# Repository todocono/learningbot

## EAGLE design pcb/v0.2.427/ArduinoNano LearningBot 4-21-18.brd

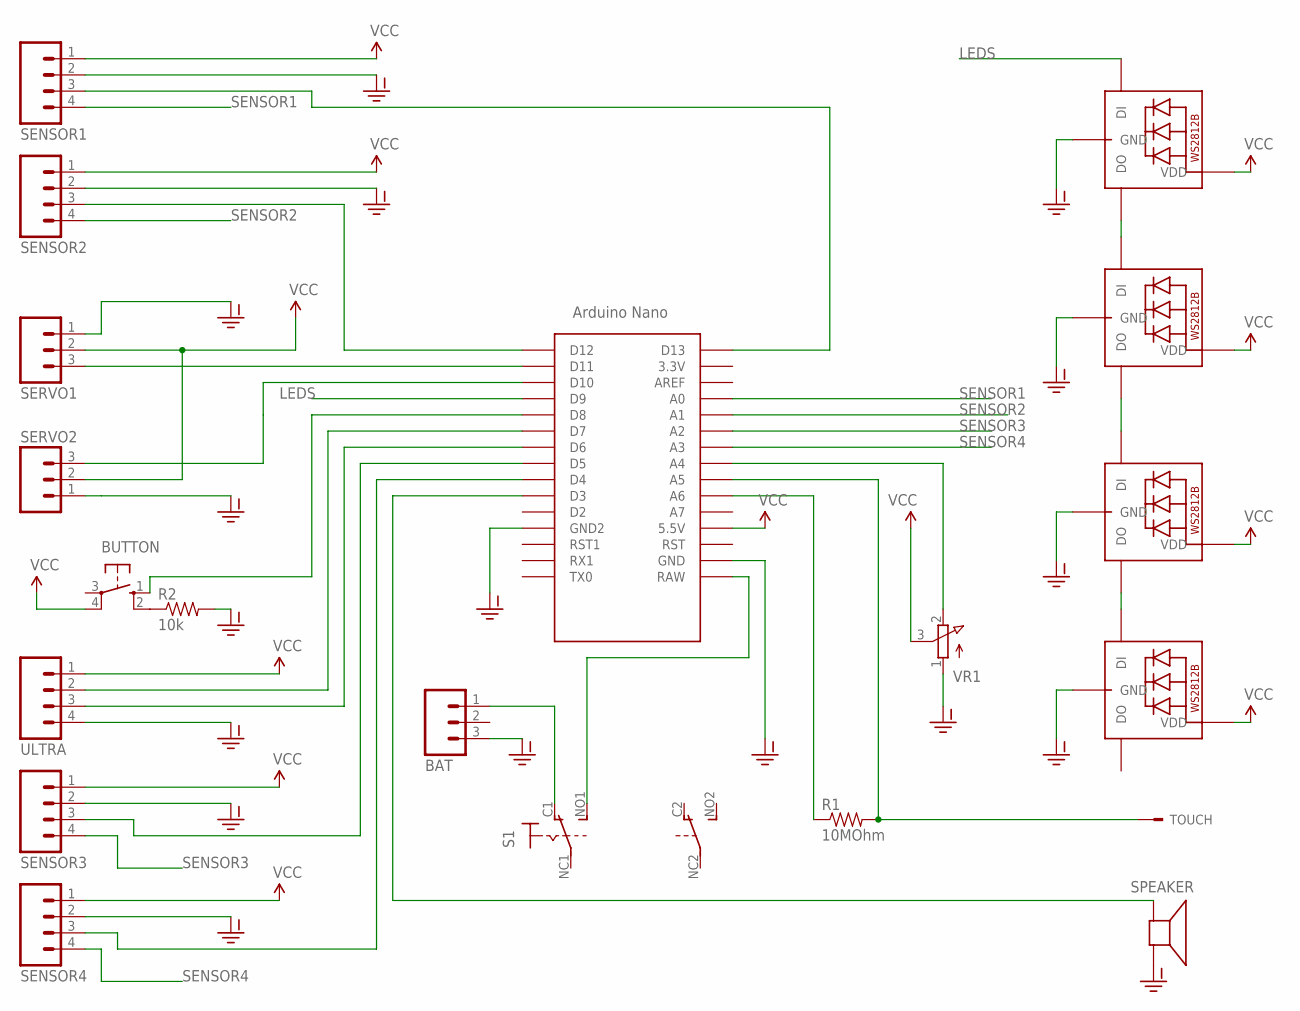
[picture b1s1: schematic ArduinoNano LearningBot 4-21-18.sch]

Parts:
BAT: M03POLAR; MOLEX-1X3
BUTTON: 10-XX; B3F-10XX
LED1, LED2, LED3, LED4: WS2812B5050; WS2812B
R1: 10MOhm; AXIAL-0.4
R2: 10k; AXIAL-0.4
S1: SWITCH_320-938; PS22F03
SENSOR1, SENSOR2, SENSOR3, SENSOR4: M04LOCK; 1X04_LOCK
SERVO1, SERVO2: M03LOCK; 1X03_LOCK
SPEAKER: SPEAKER/AL60P; AL60P
TOUCH: TOUCHSENSOR; TOUCH1
U$1: ARDUINO-CLONE_NANO
ULTRA: M04LOCK; 1X04_LOCK
VR1: 3RP/1610N-VERTICAL

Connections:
BUTTON: BUTTON.1 (S), U$1.D8
CAP_TOUCH_RECEIVE_PIN: R1.P$1 (1), U$1.A6
ECHO_PIN: U$1.D6, ULTRA.3
GND: BAT.3, LED1.3-GND (GND), LED2.3-GND (GND), LED3.3-GND (GND), LED4.3-GND (GND), R2.P$2 (2), SENSOR1.2, SENSOR2.2, SENSOR3.2, SENSOR4.2, SERVO1.1, SERVO2.1, SPEAKER.1 (+), U$1.GND, U$1.GND1 (GND2), ULTRA.4, VR1.1 (A)
IR_SENSOR1_DO: SENSOR2.3, U$1.D12
IR_SENSOR2_DO: SENSOR3.3, U$1.D5
LDR1_DO: SENSOR1.3, U$1.D13
LDR2_DO: SENSOR4.3, U$1.D4
LEDS: LED1.4-DIN (DI), U$1.D9
unnamed: LED2.2-DOUT (DO), LED3.4-DIN (DI)
unnamed: BUTTON.2 (S1), R2.P$1 (1)
unnamed: LED3.2-DOUT (DO), LED4.4-DIN (DI)
unnamed: LED1.2-DOUT (DO), LED2.4-DIN (DI)
unnamed: SERVO1.3, U$1.D11
unnamed: BAT.1, S1.C1 (O)
POTPIN: U$1.A4, VR1.2 (E)
RAWIN: S1.NO1 (S), U$1.RAW
SENSOR1: SENSOR1.4, U$1.A0
SENSOR2: SENSOR2.4, U$1.A1
SENSOR3: SENSOR3.4, U$1.A2
SENSOR4: SENSOR4.4, U$1.A3
SERVO2_PIN: SERVO2.3, U$1.D10
SPEAKERPIN: SPEAKER.2 (-), U$1.D3
TOUCH: R1.P$2 (2), TOUCH.P$1, U$1.A5
TRIG_PIN: U$1.D7, ULTRA.2
VCC: BUTTON.4 (P1), LED1.1-VDD (VDD), LED2.1-VDD (VDD), LED3.1-VDD (VDD), LED4.1-VDD (VDD), SENSOR1.1, SENSOR2.1, SENSOR3.1, SENSOR4.1, SERVO1.2, SERVO2.2, U$1.5V (5.5V), ULTRA.1, VR1.3 (S)

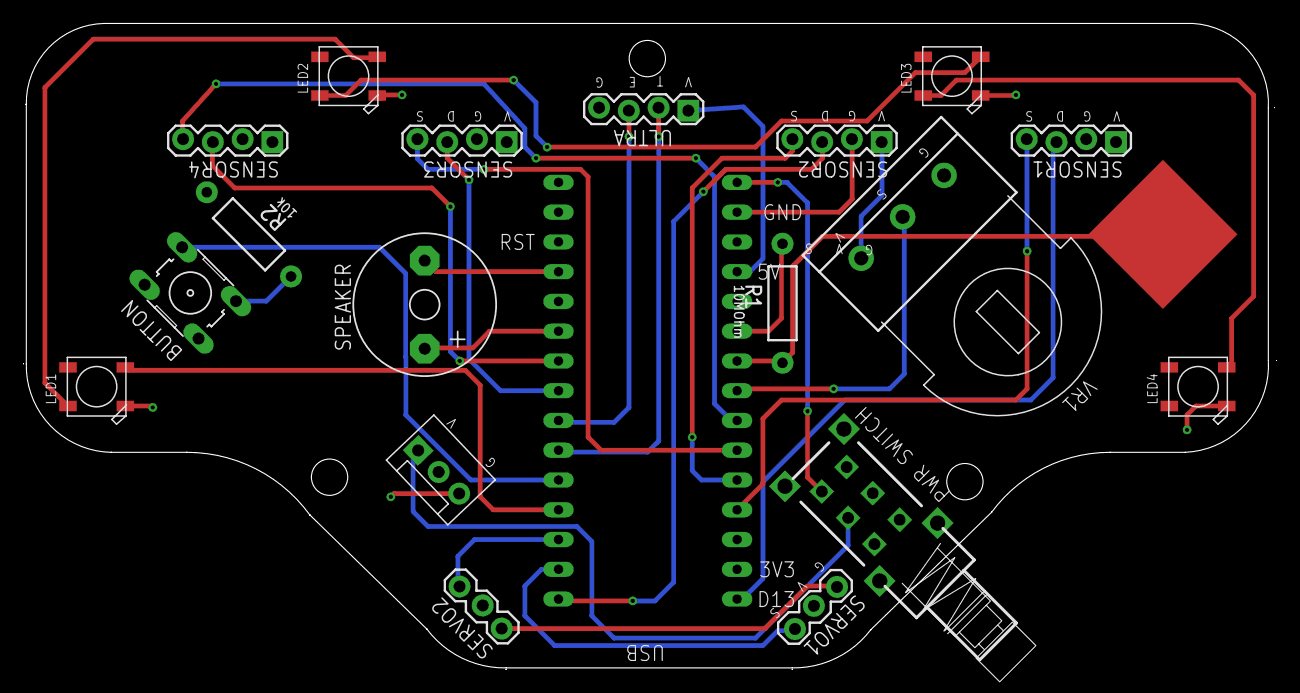
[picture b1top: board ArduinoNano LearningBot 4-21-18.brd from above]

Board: 2 copper layers, 106.9 x 55.1 mm, 20 parts (0 on the bottom side), 26 nets.

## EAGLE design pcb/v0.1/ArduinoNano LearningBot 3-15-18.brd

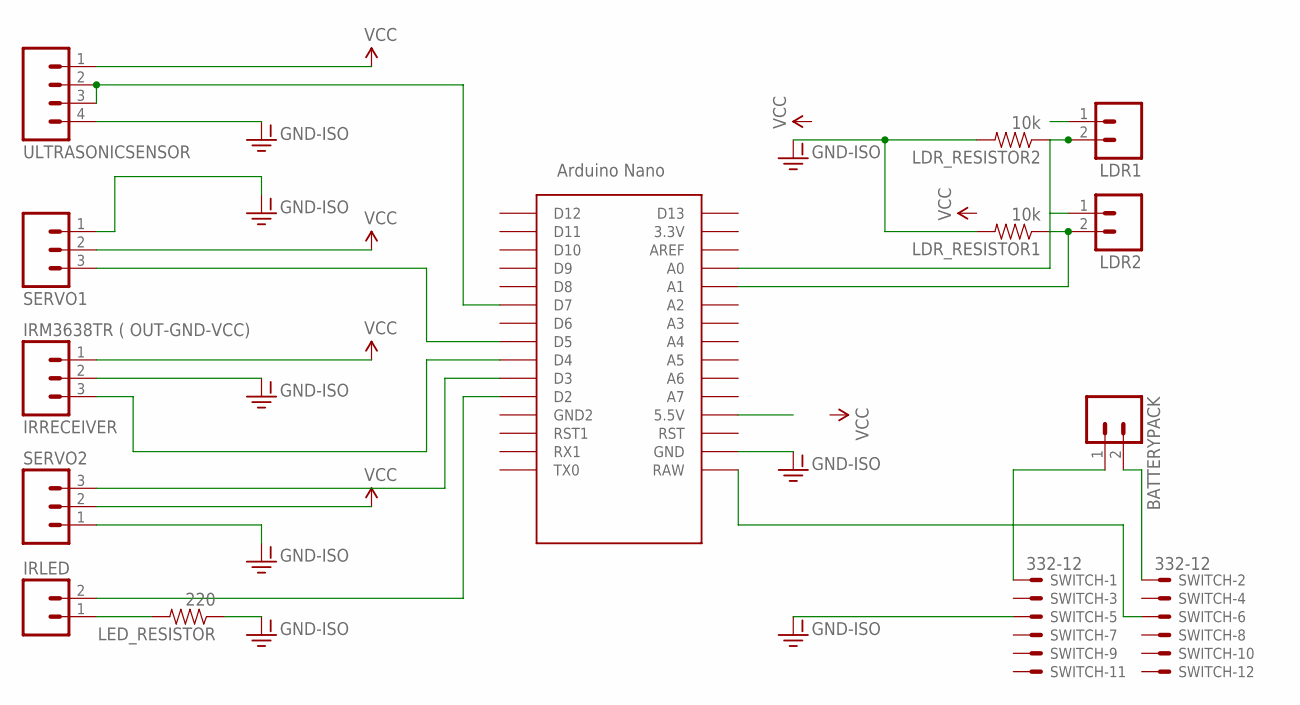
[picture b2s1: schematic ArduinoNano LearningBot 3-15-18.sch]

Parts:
BATTERYPACK: M02PTH; 1X02
IRLED: M02LOCK; 1X02_LOCK
IRRECEIVER: IRM3638TR ( OUT-GND-VCC); 1X03_LOCK
LDR1, LDR2: M02LOCK; 1X02_LOCK
LDR_RESISTOR1, LDR_RESISTOR2: 10k; AXIAL-0.4
LED_RESISTOR: 220; AXIAL-0.4
SERVO1, SERVO2: M03LOCK; 1X03_LOCK
SWITCH: 332-12
U$1: NANO
ULTRASONICSENSOR: M04LOCK; 1X04_LOCK

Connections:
A0: LDR2.2, LDR_RESISTOR1.P$1 (1), U$1.A1
A1: LDR1.2, LDR_RESISTOR2.P$1 (1), U$1.A0
ARDUINORAW: SWITCH.6, U$1.RAW
GND: BATTERYPACK.1, SWITCH.1
GND-ISO: IRRECEIVER.2, LDR_RESISTOR1.P$2 (2), LDR_RESISTOR2.P$2 (2), LED_RESISTOR.P$1 (1), SERVO1.1, SERVO2.1, U$1.GND, ULTRASONICSENSOR.4
GNDARDUINO: SWITCH.5
IRGND: IRLED.1, LED_RESISTOR.P$2 (2)
IRLED: IRLED.2, U$1.D2
IRRECEIVER: IRRECEIVER.3, U$1.D4
RAW: BATTERYPACK.2, SWITCH.2
SERVO1: SERVO1.3, U$1.D5
SERVO2: SERVO2.3, U$1.D3
ULTRASONICSENSOR: U$1.D7, ULTRASONICSENSOR.2, ULTRASONICSENSOR.3
VCC: IRRECEIVER.1, LDR1.1, LDR2.1, SERVO1.2, SERVO2.2, U$1.5V (5.5V), ULTRASONICSENSOR.1

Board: 2 copper layers, 13 parts (0 on the bottom side), 13 nets, no tracks yet.

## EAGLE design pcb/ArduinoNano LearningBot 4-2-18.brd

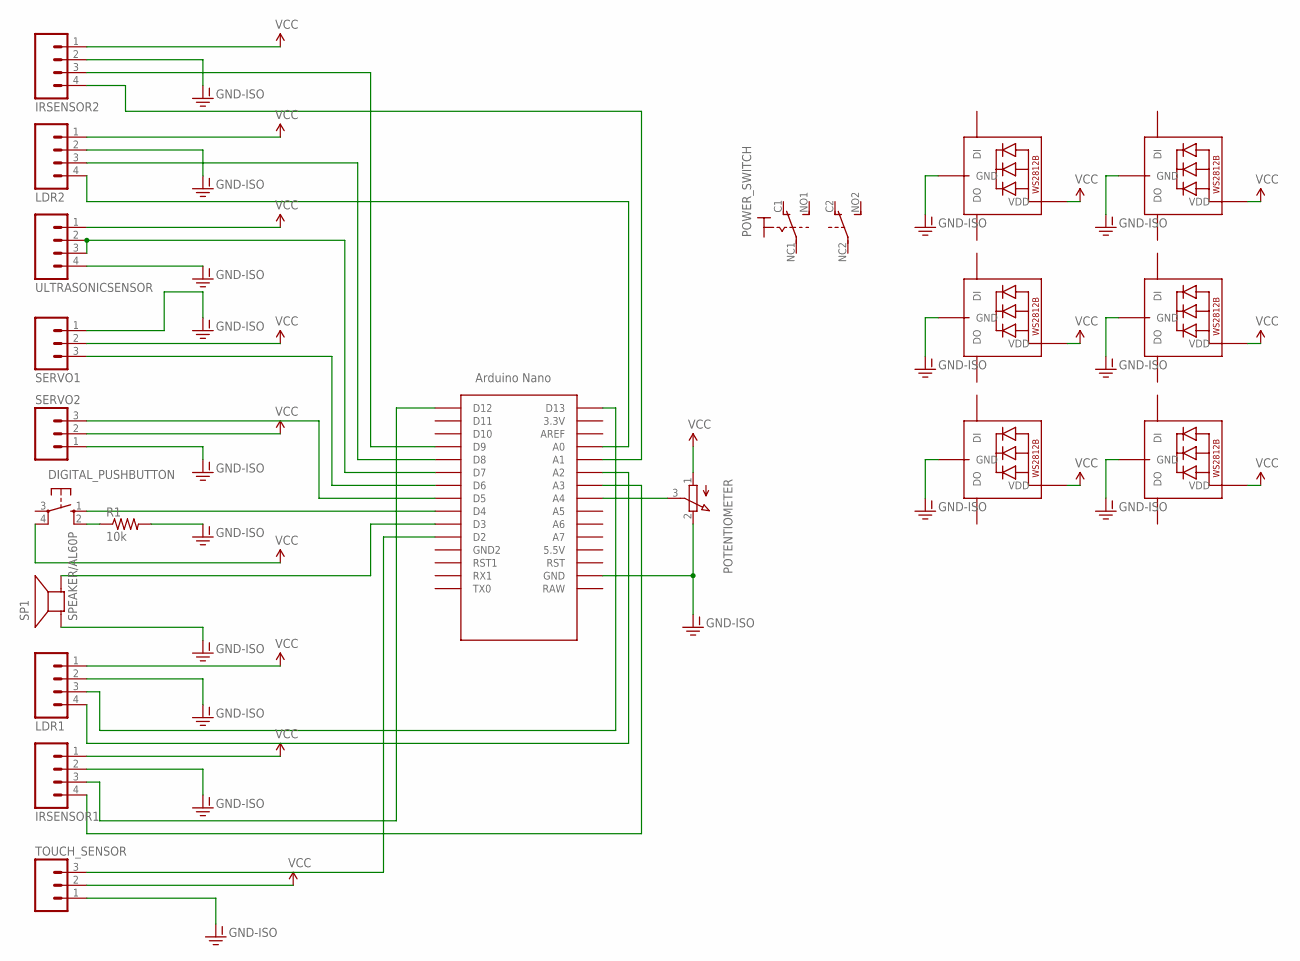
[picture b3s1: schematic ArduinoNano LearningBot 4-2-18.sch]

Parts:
DIGITAL_PUSHBUTTON: 10-XX; B3F-10XX
IRSENSOR1, IRSENSOR2: M04LOCK; 1X04_LOCK
LDR1, LDR2: M04LOCK; 1X04_LOCK
LED1, LED2, LED3, LED4, LED5, LED6: WS2812B5050; WS2812B
POTENTIOMETER: 3RP/1610N-VERTICAL
POWER_SWITCH: SWITCH_320-938; PS22F03
R1: 10k; AXIAL-0.4
SERVO1, SERVO2: M03LOCK; 1X03_LOCK
SP1: SPEAKER/AL60P; AL60P
TOUCH_SENSOR: M03LOCK; 1X03_LOCK
U$1: ARDUINO-CLONE_NANO
ULTRASONICSENSOR: M04LOCK; 1X04_LOCK

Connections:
DIGITAL_PUSHBUTTON_PIN: DIGITAL_PUSHBUTTON.1 (S), U$1.D4
GND: IRSENSOR1.2, IRSENSOR2.2, LDR1.2, LDR2.2, LED1.3-GND (GND), LED2.3-GND (GND), LED3.3-GND (GND), LED4.3-GND (GND), LED5.3-GND (GND), LED6.3-GND (GND), POTENTIOMETER.2 (E), R1.P$2 (2), SERVO1.1, SERVO2.1, SP1.1 (+), TOUCH_SENSOR.1, U$1.GND, ULTRASONICSENSOR.4
IR_SENSOR1_AO: IRSENSOR1.4, U$1.A3
IR_SENSOR1_DO: IRSENSOR1.3, U$1.D12
IR_SENSOR2_AO: IRSENSOR2.4, U$1.A1
IR_SENSOR2_DO: IRSENSOR2.3, U$1.D9
LDR1_AO: LDR1.4, U$1.A2
LDR1_DO: LDR1.3, U$1.D13
LDR2_AO: LDR2.4, U$1.A0
LDR2_DO: LDR2.3, U$1.D8
unnamed: DIGITAL_PUSHBUTTON.2 (S1), R1.P$1 (1)
unnamed: POTENTIOMETER.3 (S), U$1.A4
SERVO1_PIN: SERVO1.3, U$1.D6
SERVO2_PIN: SERVO2.3, U$1.D5
SPEAKERPIN: SP1.2 (-), U$1.D3
TOUCH_SENSOR: TOUCH_SENSOR.3, U$1.D2
ULTRASONICSENSOR_PIN: U$1.D7, ULTRASONICSENSOR.2, ULTRASONICSENSOR.3
VCC: DIGITAL_PUSHBUTTON.4 (P1), IRSENSOR1.1, IRSENSOR2.1, LDR1.1, LDR2.1, LED1.1-VDD (VDD), LED2.1-VDD (VDD), LED3.1-VDD (VDD), LED4.1-VDD (VDD), LED5.1-VDD (VDD), LED6.1-VDD (VDD), POTENTIOMETER.1 (A), SERVO1.2, SERVO2.2, TOUCH_SENSOR.2, ULTRASONICSENSOR.1

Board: 2 copper layers, 20 parts (0 on the bottom side), 18 nets, no tracks yet.

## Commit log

2018-03-30 second commit
2018-03-30 This is the first commit
    This is a schematic for Learning Bot with Arduino Nano. Note that it has a IR Reciever.
2018-03-30 third commit
2018-03-30 Here is the schematic
2018-03-30 added folders
2018-03-30 tidy up sch
2018-03-31 LearningBot Board Shape
    for illustrator
2018-03-31 footprints confirmed
2018-04-03 PCB and Schematic
2018-04-03 With components placed
2018-04-03 Better Placement
2018-04-09 Added buck converter to baord to supply current to servos
2018-04-10 gerbers
2018-04-11 added led-test
2018-04-12 added led-test v2
2018-04-12 gerber generated
2018-04-12 gerber generated v2
2018-04-20 just some changes
2018-04-20 Im not really sure
2018-04-21 Ready for inspection
2018-04-24 moved into folders, minor comments
2018-04-24 compiled library
2018-04-24 New Board
2018-04-25 Most recent
2018-04-25 component placement 95%
2018-04-25 almost there!
2018-04-26 changes to physical
2018-04-27 Howdy
2018-04-27 heyo
2018-04-27 changed designators and holes
2018-05-01 most recent board
2018-05-02 with gerbers
2018-05-02 not sure what this is
2018-05-14 Hopefully, the last one
2018-05-29 Arduino Code for Learning Bot
2018-05-30 just updating
2018-06-01 Better Arduino Code
    This code has an added function to also allow the user to test analog functions.
2018-06-06 More/better code for basic learningBot functionality
2018-06-06 ulstrasonic shouldn't bug out with this
2018-06-06 Fix so that at startup, all neopixels turn pink
2018-06-06 Even Better Fix!
2018-06-06 Even better fix
    To make all neopixels change color at the same time, I repeat the function three times. The rapid succession eliminates any rogue colors that appear before the human eye can detect them.
2018-06-07 Best code

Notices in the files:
parts and their libraries:
SparkFun-Connectors: Licensing: Creative Commons ShareAlike 4.0 International - https://creativecommons.org/licenses/by-sa/4.0
